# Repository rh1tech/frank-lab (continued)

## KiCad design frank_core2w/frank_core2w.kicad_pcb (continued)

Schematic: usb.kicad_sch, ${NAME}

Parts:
C71: 100nF; C_0603_1608Metric
C72, C73: 100uF; CP_Elec_6.3x6.0
C74, C75, C79, C81, C83: 100nF; C_0603_1608Metric; LCSC C14663
C76, C77, C78, C80, C82, C84, C86, C87, C88: 10uF; C_0603_1608Metric; LCSC C96446
C85: 1uF; C_0603_1608Metric; LCSC C29936
C89, C90: 12pF; C_0603_1608Metric; LCSC C38523
C91: 22pF; C_0603_1608Metric; LCSC C1653
J10, J11: USB4215-03-A; USB_C_Receptacle; LCSC C37616412
JP4: USB Debug; SolderJumper-2_P1.3mm_Open_RoundedPad1.0x1.5mm
JP5: PWR Debug; SolderJumper-2_P1.3mm_Open_RoundedPad1.0x1.5mm
L5: 330R 2A; L_0805_2012Metric; LCSC C76819
L6: 2.2uH; L_Cenker_CKCS3015; LCSC C167747
LD3: Green; LED_0603_1608Metric; LCSC C965804
R49: 10K; R_0603_1608Metric
R50, R51, R52, R53: 5.1K; R_0603_1608Metric; LCSC C23186
R54: 300K; R_0603_1608Metric; LCSC C23024
R55, R58, R62: 100K; R_0603_1608Metric; LCSC C25803
R56: 1M; R_0603_1608Metric; LCSC C22935; not fitted
R57, R60: 1K; R_0603_1608Metric; LCSC C21190
R59: 10K; R_0603_1608Metric; LCSC C2906982
R61: 4.7K; R_0603_1608Metric; LCSC C23162; not fitted
R63: 22K; R_0603_1608Metric; LCSC C31850
S7: SS12D00; Switch_Slide_SS12D00; Mouser Part Number 611-SK12D07VG3NS
S8: SK12D07VG3NS; Switch_Slide_SK12D07VG3NS_PWR; Mouser Part Number 611-SK12D07VG3NS; LCSC C431547
U12: TS3USB221RSER; UQFN-10
U13, U14: TPD4S012DRYR; Mouser Part Number 595-TPD4S012DRYR; LCSC C96506
U15: TPS2116DRL; SOT-583-8; LCSC C3235557
U16: AO3401A; SOT-23-3L_AOS; LCSC C15127
U17: TS3USB221RSER; UQFN-10; LCSC C130085
U18: SY8089AAAC; SOT-23-5; LCSC C78988
U19: CH334F; QFN-24-1EP_4x4mm_P0.5mm_EP2.7x2.7mm; LCSC C5187527
Y4: 12 MHz; Crystal_SMD_3225-4Pin_3.2x2.5mm; LCSC C9002

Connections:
+3V3: C71.1, C81.2, C86.1, C87.1, C91.1, JP4.1 (A), L6.1, R49.1, R57.2, R62.1, S7.2, U12.10 (VCC), U17.10 (VCC); also elsewhere on the board
/CH343P/UD+: U12.1 (1D+); also elsewhere on the board
/CH343P/UD-: U12.2 (1D-); also elsewhere on the board
/RP2350A/D+: U12.3 (2D+); also elsewhere on the board
/RP2350A/D-: U12.4 (2D-); also elsewhere on the board
/RP2350B/D+: U17.8 (D+); also elsewhere on the board
/RP2350B/D-: U17.7 (D-); also elsewhere on the board
/USB/+5V_BUCK: C80.1, C82.1, C83.1, L5.2, U18.1 (EN), U18.4 (IN)
/USB/D2+: J10.6 (DP1), J10.8 (DP2), U13.1 (D+), U17.1 (1D+)
/USB/D2-: J10.5 (DN2), J10.7 (DN1), U13.2 (D-_), U17.2 (1D-)
/USB/DH+: U17.3 (2D+), U19.15 (DPU+)
/USB/DH-: U17.4 (2D-), U19.14 (DMU-)
/USB/DS1+: U19.12 (DP1+); also elsewhere on the board
/USB/DS1-: U19.11 (DM1-); also elsewhere on the board
/USB/DS2+: U19.10 (DP2+); also elsewhere on the board
/USB/DS2-: U19.9 (DM2-); also elsewhere on the board
/USB/DS3+: U19.8 (DP3+); also elsewhere on the board
/USB/DS3-: U19.7 (DM3-); also elsewhere on the board
/USB/OVCUR: U19.1 (~OVCUR); also elsewhere on the board
/USB/PWREN: U19.24 (~PWREN); also elsewhere on the board
/USB/S: JP4.2 (B), R59.2, S7.3, U17.9 (S)
/USB/ST: R56.2, U15.8 (ST)
/USB/USBC_D+: J11.6 (DP1), J11.8 (DP2), U12.8 (D+), U14.1 (D+)
/USB/USBC_D-: J11.5 (DN2), J11.7 (DN1), U12.7 (D-), U14.2 (D-_)
/USB/VBUS_IN: C78.1, C79.2, R58.2, U15.2 (VOUT), U15.7 (VOUT), U16.2 (S)
/USB/VBUS_IN1: C74.2, C76.2, J11.2 (VBUS), J11.11 (VBUS), R54.2, U14.6 (VBUS), U15.3 (VIN1), U15.5 (MODE)
/USB/VBUS_IN2: C75.2, C77.2, J10.2 (VBUS), J10.11 (VBUS), U13.6 (VBUS), U15.6 (VIN2)
/USB/VDD33: C84.2, C85.2, U19.20 (VDD33_{LDO})
/USB/XTAL_N: C89.1, U19.3 (XO), Y4.3
/USB/XTAL_P: C90.1, U19.4 (XI), Y4.1
/USB_SEL: R49.2, U12.9 (S); also elsewhere on the board
GND: C71.2, C72.2, C73.2, C74.1, C75.1, C76.1, C77.1, C78.2, C80.2, C81.1, C82.2, C83.2, C84.1, C85.1, C86.2, C87.2, C88.1, C89.2, C90.2, J10.1 (GND), J10.12 (GND), J10.13 (SHIELD), J11.1 (GND), J11.12 (GND), J11.13 (SHIELD), JP5.1 (A), LD3.1 (K), R50.1, R51.1, R52.1, R53.1, R55.1, R59.1, R61.2, R63.2, S8.2, U12.5 (GND), U12.6 (~OE), U13.4 (GND), U14.4 (GND), U15.1 (GND), U17.5 (GND), U17.6 (~OE), U18.2 (GND), U19.25 (GND), Y4.2, Y4.4; also elsewhere on the board
unnamed: J10.4 (CC1), R50.2
unnamed: J10.10 (CC2), R51.2
unnamed: J11.4 (CC1), R52.2
unnamed: J11.10 (CC2), R53.2
unnamed: JP5.2 (B), R60.2, S8.3
unnamed: LD3.2 (A), R57.1
unnamed: R54.1, R55.2, R56.1, U15.4 (PR1)
unnamed: C79.1, R58.1, R60.1, U16.1 (G)
unnamed: C91.2, R62.2, R63.1, U18.5 (FB)
unnamed: L6.2, U18.3 (LX)
unnamed: R61.1, U19.18 (PSELF)
VBUS: C72.1, C73.1, C88.2, L5.1, U16.3 (D), U19.19 (V5); also elsewhere on the board

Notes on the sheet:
USB-A shared VBUS bulk: C102 + C103 = 200 uF USB 2.0 7.2.4.1: >= 120 uF per hub, may be shared Kyocera AVX APZ0606101M016R 100 uF 16 V aluminium polymer, ESR 30 mOhm

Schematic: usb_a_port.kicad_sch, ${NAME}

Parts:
C95: 100nF; C_0603_1608Metric; LCSC C14663
C96: 10uF; C_0603_1608Metric; LCSC C96446
J12: 676430910; USB_A_Short; LCSC C2798029
R65: 100K; R_0603_1608Metric; LCSC C25803
U21: TPD4S012DRYR; Mouser Part Number 595-TPD4S012DRYR; LCSC C96506
U22: CH217K; SOT-23-6; LCSC C7462749

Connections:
/USB/DS1+: J12.3 (D+), U21.1 (D+); also elsewhere on the board
/USB/DS1-: J12.2 (D-), U21.2 (D-_); also elsewhere on the board
/USB/OVCUR: U22.3 (FLAG#); also elsewhere on the board
/USB/PWREN: U22.4 (EN#); also elsewhere on the board
/USB/USB A Port 1/VBUS_P: C95.1, J12.1 (VBUS), U21.6 (VBUS), U22.1 (VOUT)
GND: C95.2, C96.1, J12.4 (GND), J12.5 (Shield), R65.1, U21.4 (GND), U22.2 (GND); also elsewhere on the board
unnamed: R65.2, U22.5 (ISET)
VBUS: C96.2, U22.6 (VIN); also elsewhere on the board

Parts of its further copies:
C97, C99: 100nF; C_0603_1608Metric; LCSC C14663
C98, C101: 10uF; C_0603_1608Metric; LCSC C96446
J13, J14: 676430910; USB_A_Short; LCSC C2798029
R66, R70: 100K; R_0603_1608Metric; LCSC C25803
U23, U25: TPD4S012DRYR; Mouser Part Number 595-TPD4S012DRYR; LCSC C96506
U24, U27: CH217K; SOT-23-6; LCSC C7462749

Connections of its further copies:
/USB/DS2+: J13.3 (D+), U23.1 (D+); also elsewhere on the board
/USB/DS2-: J13.2 (D-), U23.2 (D-_); also elsewhere on the board
/USB/DS3+: J14.3 (D+), U25.1 (D+); also elsewhere on the board
/USB/DS3-: J14.2 (D-), U25.2 (D-_); also elsewhere on the board
/USB/OVCUR: U24.3 (FLAG#), U27.3 (FLAG#); also elsewhere on the board
/USB/PWREN: U24.4 (EN#), U27.4 (EN#); also elsewhere on the board
/USB/USB A Port 2/VBUS_P: C97.1, J13.1 (VBUS), U23.6 (VBUS), U24.1 (VOUT)
/USB/USB A Port 3/VBUS_P: C99.1, J14.1 (VBUS), U25.6 (VBUS), U27.1 (VOUT)
GND: C97.2, C98.1, C99.2, C101.1, J13.4 (GND), J13.5 (Shield), J14.4 (GND), J14.5 (Shield), R66.1, R70.1, U23.4 (GND), U24.2 (GND), U25.4 (GND), U27.2 (GND); also elsewhere on the board
unnamed: R66.2, U24.5 (ISET)
unnamed: R70.2, U27.5 (ISET)
VBUS: C98.2, C101.2, U24.6 (VIN), U27.6 (VIN); also elsewhere on the board

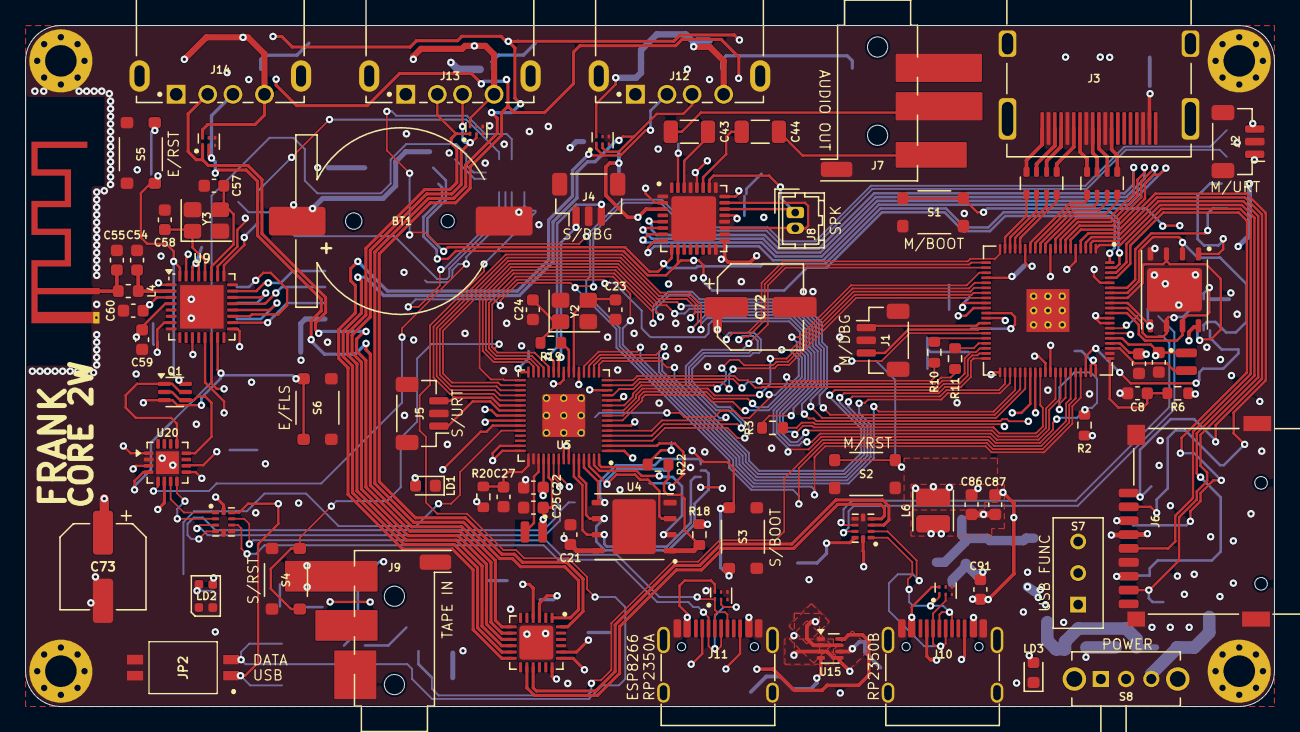
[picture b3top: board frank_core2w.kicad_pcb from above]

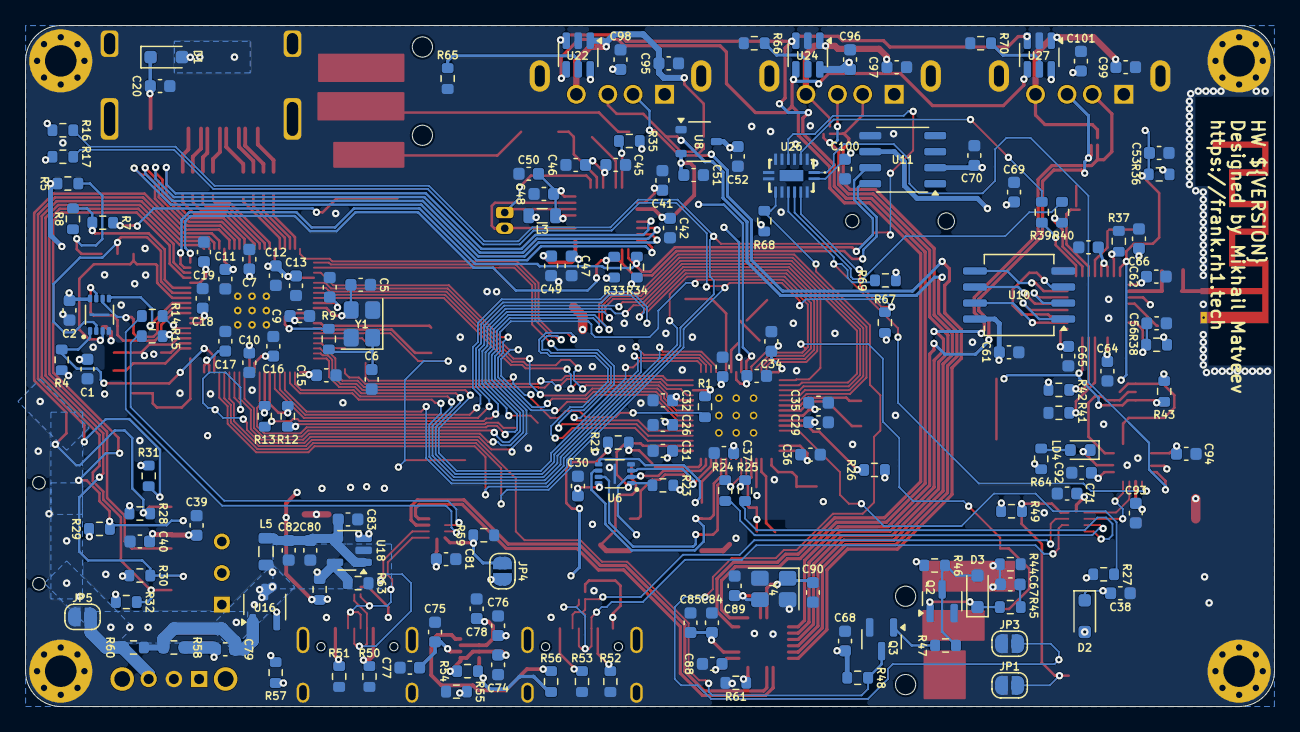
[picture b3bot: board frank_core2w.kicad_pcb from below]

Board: 4 copper layers, 99.0 x 54.0 mm, 253 parts (165 on the bottom side), 203 nets.

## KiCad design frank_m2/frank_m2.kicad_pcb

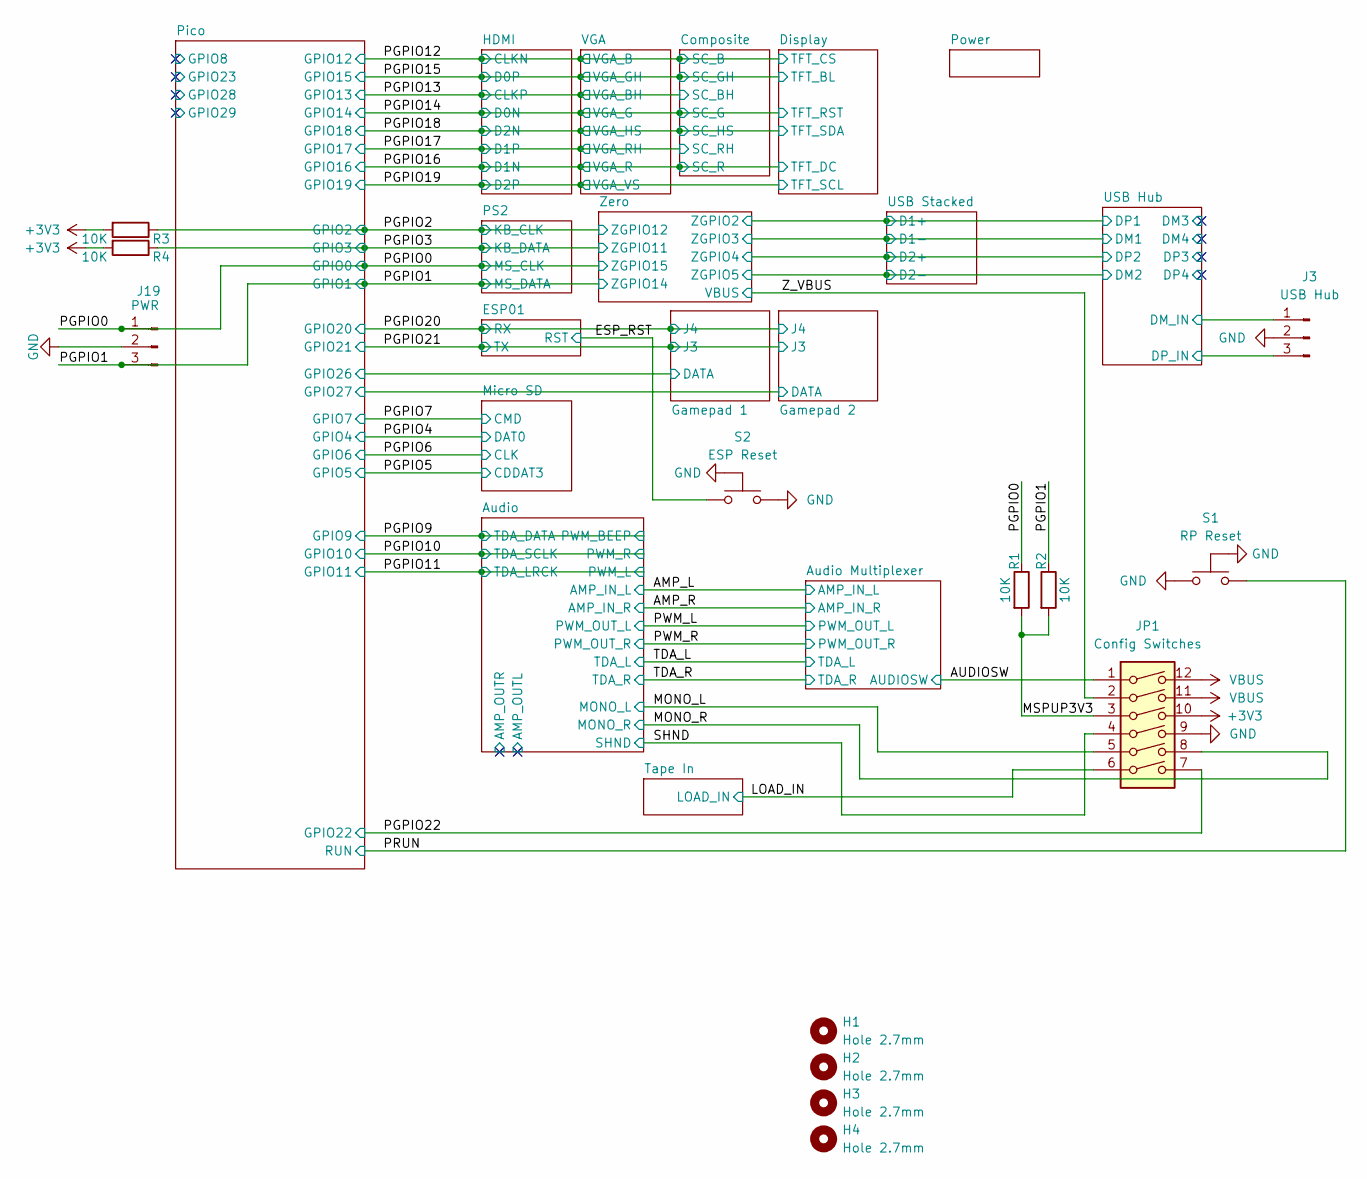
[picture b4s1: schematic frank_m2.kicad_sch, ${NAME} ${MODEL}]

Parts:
H1, H2, H3, H4: Hole 2.7mm; MountingHole_2.7mm
J3: USB Hub; JST_SH_1x03_P1.00mm_Vertical
J19: PWR; JST_SH_1x03_P1.00mm_Vertical_UART
JP1: Config Switches; SOIC-12_P1.27mm
R1, R2, R3, R4: 10K; R_0805_2012Metric
S1: RP Reset; Button_SMD_TS1234VW
S2: ESP Reset; Button_SMD_TS1234VW

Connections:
+3V3: JP1.10, R3.2, R4.2; also elsewhere on the board
/AUDIOSW: JP1.1; also elsewhere on the board
/ESP_RST: S2.1; also elsewhere on the board
/LOAD_IN: JP1.6; also elsewhere on the board
/MONO_L: JP1.5; also elsewhere on the board
/MONO_R: JP1.8; also elsewhere on the board
/MSPUP3V3: JP1.3, R1.2, R2.2
/PGPIO0: J19.1, R1.1; also elsewhere on the board
/PGPIO1: J19.3, R2.1; also elsewhere on the board
/PGPIO2: R3.1; also elsewhere on the board
/PGPIO3: R4.1; also elsewhere on the board
/PGPIO22: JP1.7; also elsewhere on the board
/PRUN: S1.1; also elsewhere on the board
/SHND: JP1.4; also elsewhere on the board
/USB Hub/DM_IN: J3.1; also elsewhere on the board
/USB Hub/DP_IN: J3.3; also elsewhere on the board
/Z_VBUS: JP1.2; also elsewhere on the board
GND: J3.2, J19.2, JP1.9, S1.2, S1.3 (GND), S2.2, S2.3 (GND); also elsewhere on the board
VBUS: JP1.11, JP1.12; also elsewhere on the board

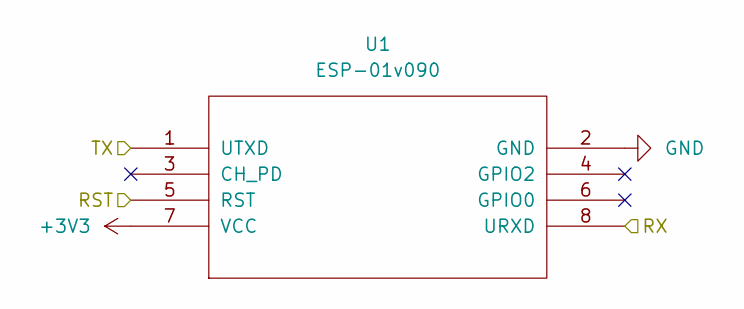
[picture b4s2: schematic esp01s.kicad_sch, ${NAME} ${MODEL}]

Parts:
U1: ESP-01v090; ESP-01

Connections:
+3V3: U1.7 (VCC); also elsewhere on the board
/ESP_RST: U1.5 (RST); also elsewhere on the board
/PGPIO20: U1.8 (URXD); also elsewhere on the board
/PGPIO21: U1.1 (UTXD); also elsewhere on the board
GND: U1.2 (GND); also elsewhere on the board

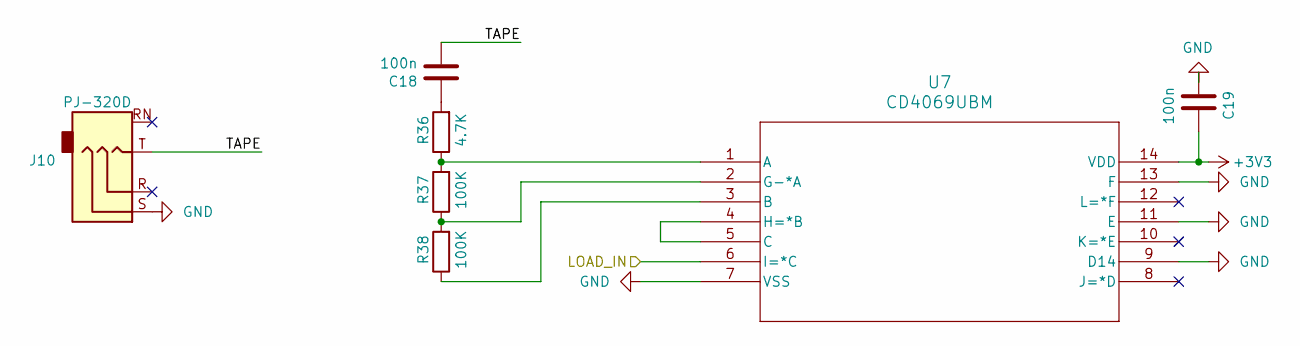
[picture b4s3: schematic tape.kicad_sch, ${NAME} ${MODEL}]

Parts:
C18, C19: 100n; C_0805_2012Metric
J10: PJ-320D; AudioJack_3.5mm_PJ320D
R36: 4.7K; R_0805_2012Metric
R37, R38: 100K; R_0805_2012Metric
U7: CD4069UBM; SOIC-14_P1.27mm

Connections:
+3V3: C19.1, U7.14 (VDD); also elsewhere on the board
/LOAD_IN: U7.6 (I=*C); also elsewhere on the board
/Tape In/TAPE: C18.2, J10.T
GND: C19.2, J10.S, U7.7 (VSS), U7.9 (D14), U7.11 (E), U7.13 (F); also elsewhere on the board
unnamed: C18.1, R36.2
unnamed: R36.1, R37.2, U7.1 (A)
unnamed: R38.1, U7.3 (B)
unnamed: U7.4 (H=*B), U7.5 (C)
unnamed: R37.1, R38.2, U7.2 (G-*A)

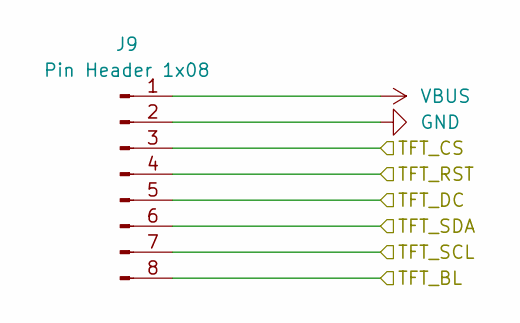
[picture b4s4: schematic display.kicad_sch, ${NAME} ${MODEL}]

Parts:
J9: Pin Header 1x08; JST_GH_1x08_P1.25mm

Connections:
/PGPIO12: J9.3; also elsewhere on the board
/PGPIO14: J9.4; also elsewhere on the board
/PGPIO15: J9.8; also elsewhere on the board
/PGPIO16: J9.5; also elsewhere on the board
/PGPIO18: J9.6; also elsewhere on the board
/PGPIO19: J9.7; also elsewhere on the board
GND: J9.2; also elsewhere on the board
VBUS: J9.1; also elsewhere on the board

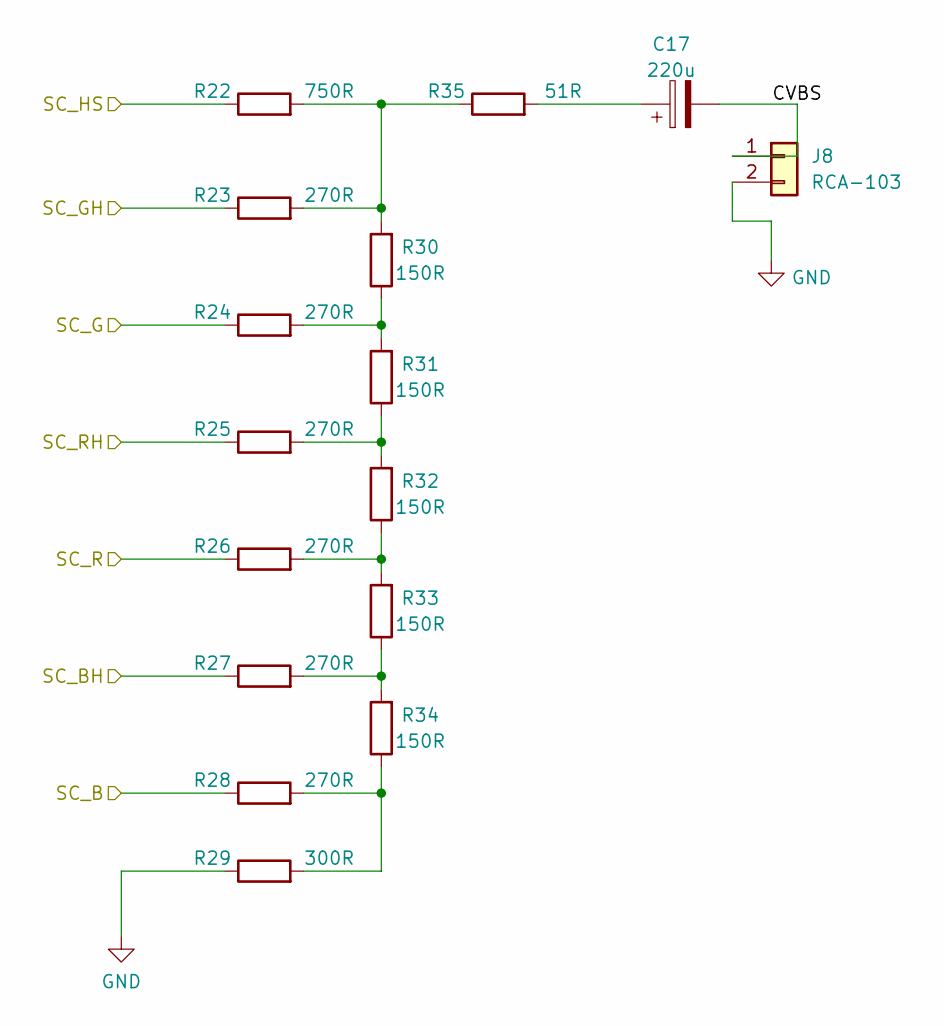
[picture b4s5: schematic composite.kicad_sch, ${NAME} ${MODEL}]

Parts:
C17: 220u; C_Radial_D6.3mm_P2.50mm
J8: RCA-103; BarrelJack_RCJ-012
R22: 750R; R_0805_2012Metric
R23, R24, R25, R26, R27, R28: 270R; R_0805_2012Metric
R29: 300R; R_0805_2012Metric
R30, R31, R32, R33, R34: 150R; R_0805_2012Metric
R35: 51R; R_0805_2012Metric

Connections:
/Composite/CVBS: C17.2, J8.1
/PGPIO12: R28.1; also elsewhere on the board
/PGPIO13: R27.1; also elsewhere on the board
/PGPIO14: R24.1; also elsewhere on the board
/PGPIO15: R23.1; also elsewhere on the board
/PGPIO16: R26.1; also elsewhere on the board
/PGPIO17: R25.1; also elsewhere on the board
/PGPIO18: R22.1; also elsewhere on the board
GND: J8.2, R29.1; also elsewhere on the board
unnamed: C17.1, R35.2
unnamed: R22.2, R23.2, R30.2, R35.1
unnamed: R24.2, R30.1, R31.2
unnamed: R25.2, R31.1, R32.2
unnamed: R26.2, R32.1, R33.2
unnamed: R27.2, R33.1, R34.2
unnamed: R28.2, R29.2, R34.1

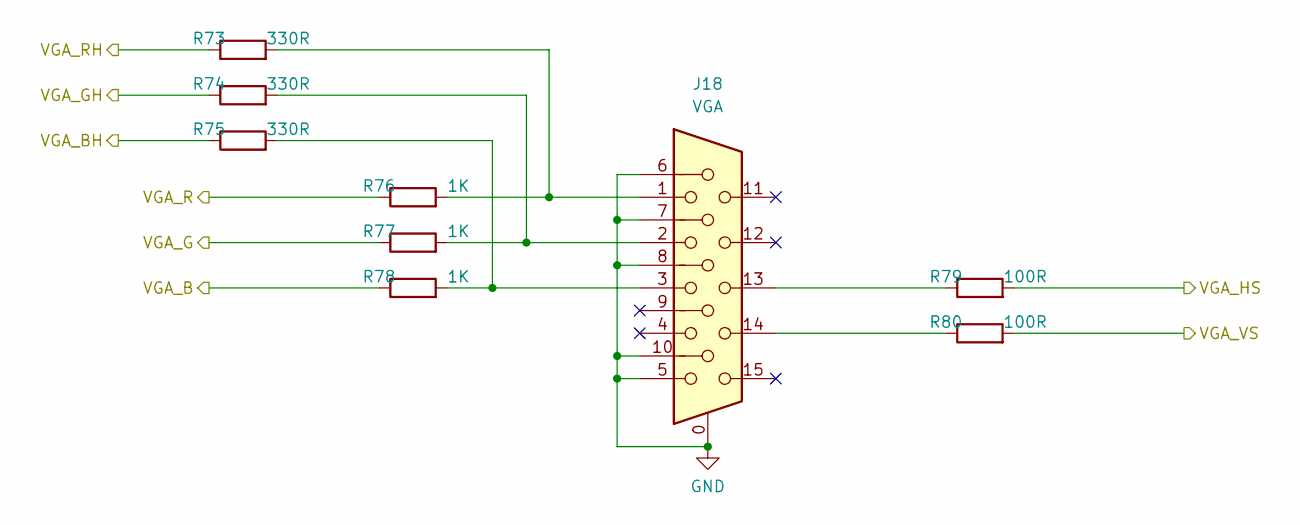
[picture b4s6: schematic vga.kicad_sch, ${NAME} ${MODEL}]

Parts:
J18: VGA; DSUB-15_Female
R73, R74, R75: 330R; R_0805_2012Metric
R76, R77, R78: 1K; R_0805_2012Metric
R79, R80: 100R; R_0805_2012Metric

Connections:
/PGPIO12: R78.1; also elsewhere on the board
/PGPIO13: R75.1; also elsewhere on the board
/PGPIO14: R77.1; also elsewhere on the board
/PGPIO15: R74.1; also elsewhere on the board
/PGPIO16: R76.1; also elsewhere on the board
/PGPIO17: R73.1; also elsewhere on the board
/PGPIO18: R79.2; also elsewhere on the board
/PGPIO19: R80.2; also elsewhere on the board
GND: J18.0, J18.5, J18.6, J18.7, J18.8, J18.10; also elsewhere on the board
unnamed: J18.1, R73.2, R76.2
unnamed: J18.2, R74.2, R77.2
unnamed: J18.3, R75.2, R78.2
unnamed: J18.13, R79.1
unnamed: J18.14, R80.1

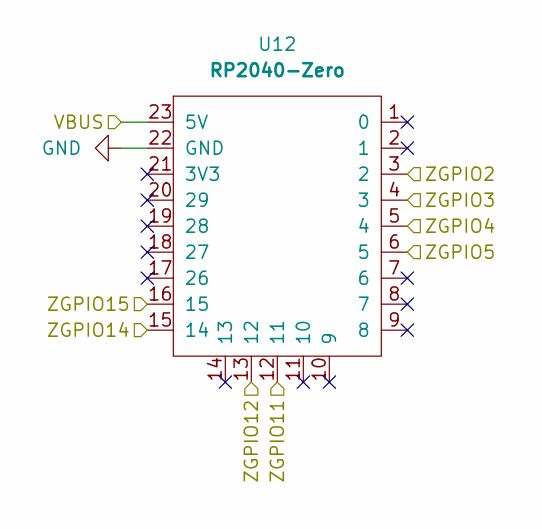
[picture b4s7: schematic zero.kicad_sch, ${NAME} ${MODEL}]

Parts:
U12: RP2040-Zero; RaspberryPi_Zero

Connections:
/PGPIO0: U12.16 (15); also elsewhere on the board
/PGPIO1: U12.15 (14); also elsewhere on the board
/PGPIO2: U12.13 (12); also elsewhere on the board
/PGPIO3: U12.12 (11); also elsewhere on the board
/USB Hub/DM1: U12.4 (3); also elsewhere on the board
/USB Hub/DM2: U12.6 (5); also elsewhere on the board
/USB Hub/DP1: U12.3 (2); also elsewhere on the board
/USB Hub/DP2: U12.5 (4); also elsewhere on the board
/Z_VBUS: U12.23 (5V); also elsewhere on the board
GND: U12.22 (GND); also elsewhere on the board

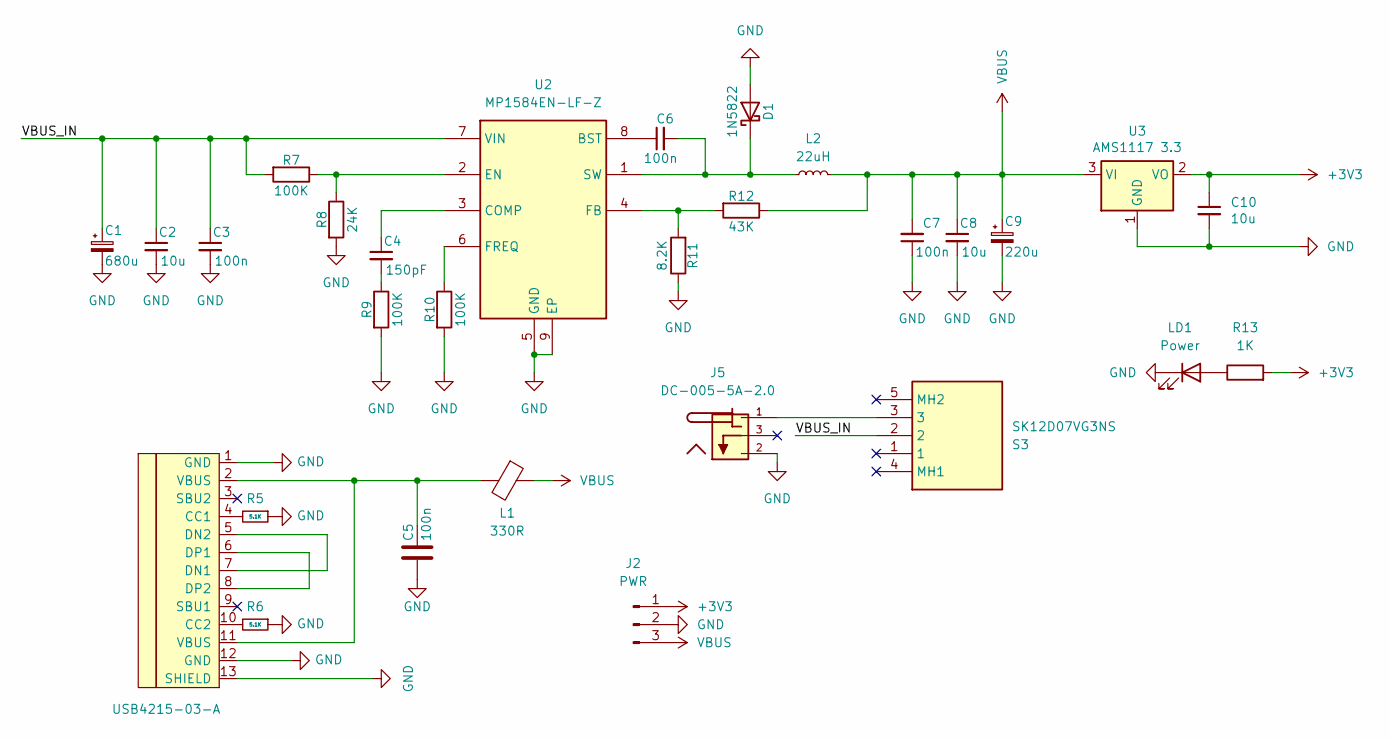
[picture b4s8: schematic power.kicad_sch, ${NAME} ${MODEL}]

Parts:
C1: 680u; C_Radial_D8.0mm_P3.50mm
C2, C8, C10: 10u; C_0805_2012Metric
C3, C5, C6, C7: 100n; C_0805_2012Metric
C4: 150pF; R_0805_2012Metric
C9: 220u; C_Radial_D6.3mm_P2.50mm
D1: 1N5822; D_SMA
J2: PWR; PinHeader_1x03_P2.54mm
J4: USB4215-03-A; USB_C_Receptacle; LCSC C165948
J5: DC-005-5A-2.0; BarrelJack_DC-005; PARTREV A0
L1: 330R; R_0805_2012Metric
L2: 22uH; Inductor_CDRH104RNP
LD1: Power; LED_0805
R5, R6: 5.1K; R_0805_2012Metric
R7, R9, R10: 100K; R_0805_2012Metric
R8: 24K; R_0805_2012Metric
R11: 8.2K; R_0805_2012Metric
R12: 43K; R_0805_2012Metric
R13: 1K; R_0805_2012Metric
S3: SK12D07VG3NS; Switch_Slide_SK12D07VG3NS; Mouser Part Number 611-SK12D07VG3NS
U2: MP1584EN-LF-Z; SOIC-9_P1.27mm; Mouser Part Number 946-MP1584ENLFZ
U3: AMS1117 3.3; SOT-223

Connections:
+3V3: C10.1, J2.1, R13.2, U3.2 (VO); also elsewhere on the board
/Power/VBUS_IN: C1.1, C2.1, C3.1, R7.2, S3.2, U2.7 (VIN)
GND: C1.2, C2.2, C3.2, C5.2, C7.1, C8.2, C9.2, C10.2, D1.2 (A), J2.2, J4.1 (GND), J4.12 (GND), J4.13 (SHIELD), J5.2, LD1.1 (K), R5.1, R6.1, R8.2, R9.2, R10.2, R11.1, U2.5 (GND), U2.9 (EP), U3.1 (GND); also elsewhere on the board
unnamed: C4.2, R9.1
unnamed: C5.1, J4.2 (VBUS), J4.11 (VBUS), L1.2
unnamed: C6.2, D1.1 (K), L2.1, U2.1 (SW)
unnamed: J4.4 (CC1), R5.2
unnamed: J4.10 (CC2), R6.2
unnamed: J4.5 (DN2), J4.7 (DN1)
unnamed: J4.6 (DP1), J4.8 (DP2)
unnamed: J5.1, S3.3
unnamed: LD1.2 (A), R13.1
unnamed: C6.1, U2.8 (BST)
unnamed: C4.1, U2.3 (COMP)
unnamed: R7.1, R8.1, U2.2 (EN)
unnamed: R11.2, R12.2, U2.4 (FB)
unnamed: R10.1, U2.6 (FREQ)
VBUS: C7.2, C8.1, C9.1, J2.3, L1.1, L2.2, R12.1, U3.3 (VI); also elsewhere on the board

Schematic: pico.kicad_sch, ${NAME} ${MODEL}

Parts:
JP2: 3V3 Jumper; Jumper_Solder
U6: Rasberry Pi Pico 1/2; RaspberryPi_Pico

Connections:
+3V3: JP2.2 (B); also elsewhere on the board
/Gamepad 1/DATA: U6.31 (GPIO26_ADC0); also elsewhere on the board
/Gamepad 2/DATA: U6.32 (GPIO27_ADC1); also elsewhere on the board
/PGPIO0: U6.1 (GPIO0); also elsewhere on the board
/PGPIO1: U6.2 (GPIO1); also elsewhere on the board
/PGPIO2: U6.4 (GPIO2); also elsewhere on the board
/PGPIO3: U6.5 (GPIO3); also elsewhere on the board
/PGPIO4: U6.6 (GPIO4); also elsewhere on the board
/PGPIO5: U6.7 (GPIO5); also elsewhere on the board
/PGPIO6: U6.9 (GPIO6); also elsewhere on the board
/PGPIO7: U6.10 (GPIO7); also elsewhere on the board
/PGPIO9: U6.12 (GPIO9); also elsewhere on the board
/PGPIO10: U6.14 (GPIO10); also elsewhere on the board
/PGPIO11: U6.15 (GPIO11); also elsewhere on the board
/PGPIO12: U6.16 (GPIO12); also elsewhere on the board
/PGPIO13: U6.17 (GPIO13); also elsewhere on the board
/PGPIO14: U6.19 (GPIO14); also elsewhere on the board
/PGPIO15: U6.20 (GPIO15); also elsewhere on the board
/PGPIO16: U6.21 (GPIO16); also elsewhere on the board
/PGPIO17: U6.22 (GPIO17); also elsewhere on the board
/PGPIO18: U6.24 (GPIO18); also elsewhere on the board
/PGPIO19: U6.25 (GPIO19); also elsewhere on the board
/PGPIO20: U6.26 (GPIO20); also elsewhere on the board
/PGPIO21: U6.27 (GPIO21); also elsewhere on the board
/PGPIO22: U6.29 (GPIO22); also elsewhere on the board
/PRUN: U6.30 (RUN); also elsewhere on the board
/Pico/GPIO8: U6.11 (GPIO8)
/Pico/GPIO8_1: U6.11 (GPIO8)
/Pico/GPIO23: U6.37 (3V3_EN)
/Pico/GPIO23_1: U6.37 (3V3_EN)
/Pico/GPIO28: U6.34 (GPIO28_ADC2)
/Pico/GPIO28_1: U6.34 (GPIO28_ADC2)
/Pico/GPIO29: U6.35 (ADC_VREF)
/Pico/GPIO29_1: U6.35 (ADC_VREF)
GND: U6.3 (GND), U6.8 (GND), U6.13 (GND), U6.18 (GND), U6.23 (GND), U6.28 (GND), U6.33 (AGND), U6.38 (GND); also elsewhere on the board
unnamed: JP2.1 (A), U6.36 (3V3)
VBUS: U6.40 (VBUS); also elsewhere on the board

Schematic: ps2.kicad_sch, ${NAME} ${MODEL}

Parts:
C11, C12, C13, C14: 100n; C_0805_2012Metric
J6: MDC-036; MiniDIN_6pin_Female
U4: TXS0104EDR; SOIC-14_P1.27mm; Mouser Part Number 595-TXS0104EDR

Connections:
+3V3: C12.1, C13.1, U4.1 (VCCA), U4.8 (OE); also elsewhere on the board
/PGPIO0: U4.4 (A3); also elsewhere on the board
/PGPIO1: U4.5 (A4); also elsewhere on the board
/PGPIO2: U4.2 (A1); also elsewhere on the board
/PGPIO3: U4.3 (A2); also elsewhere on the board
/PS2/KB_CLK_5V: J6.5, U4.13 (B1)
/PS2/KB_DATA_5V: J6.1, U4.12 (B2)
/PS2/MS_CLK_5V: J6.6, U4.11 (B3)
/PS2/MS_DATA_5V: J6.2, U4.10 (B4)
GND: C11.2, C12.2, C13.2, C14.2, J6.3, U4.7 (GND); also elsewhere on the board
VBUS: C11.1, C14.1, J6.4, U4.14 (VCCB); also elsewhere on the board

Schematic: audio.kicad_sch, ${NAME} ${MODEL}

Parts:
J11: PAM L; JST_GH_1x02_P1.25mm
J12: PAM R; JST_GH_1x02_P1.25mm
J13: PJ-320D; AudioJack_3.5mm_PJ320D

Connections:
/Audio/AMP_OUTL: J13.T; also elsewhere on the board
/Audio/AMP_OUTR: J13.R; also elsewhere on the board
/Audio/AMP_PAM_OUTL_M: J11.2; also elsewhere on the board
/Audio/AMP_PAM_OUTL_P: J11.1; also elsewhere on the board
/Audio/AMP_PAM_OUTR_M: J12.2; also elsewhere on the board
/Audio/AMP_PAM_OUTR_P: J12.1; also elsewhere on the board
GND: J13.S; also elsewhere on the board

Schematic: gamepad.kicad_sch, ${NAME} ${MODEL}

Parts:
D3: 3V3; D_miniMELF
J14: GP2; DSUB-9_Male_TopMount
R67: 1K; R_0805_2012Metric

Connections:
/Gamepad 1/DATA: D3.1 (K), R67.1; also elsewhere on the board
/PGPIO20: J14.4; also elsewhere on the board
/PGPIO21: J14.3; also elsewhere on the board
GND: D3.2 (A), J14.8; also elsewhere on the board
unnamed: J14.2, R67.2
VBUS: J14.6; also elsewhere on the board

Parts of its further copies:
D4: 3V3; D_miniMELF
J15: GP2; DSUB-9_Male_TopMount
R68: 1K; R_0805_2012Metric

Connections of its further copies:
/Gamepad 2/DATA: D4.1 (K), R68.1; also elsewhere on the board
/PGPIO20: J15.4; also elsewhere on the board
/PGPIO21: J15.3; also elsewhere on the board
GND: D4.2 (A), J15.8; also elsewhere on the board
unnamed: J15.2, R68.2
VBUS: J15.6; also elsewhere on the board

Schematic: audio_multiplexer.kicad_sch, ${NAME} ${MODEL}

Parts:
C37: 100n; C_0805_2012Metric
R66: 10K; R_0805_2012Metric
U11: 74HC4052D; SOP-16_P1.27mm; Mouser Part Number 771-74HC4052D-T

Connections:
/AMP_L: U11.13 (1Z); also elsewhere on the board
/AMP_R: U11.3 (2Z); also elsewhere on the board
/AUDIOSW: R66.2, U11.10 (S0); also elsewhere on the board
/PWM_L: U11.12 (1Y0); also elsewhere on the board
/PWM_R: U11.1 (2Y0); also elsewhere on the board
/TDA_L: U11.14 (1Y1); also elsewhere on the board
/TDA_R: U11.5 (2Y1); also elsewhere on the board
GND: C37.1, R66.1, U11.2 (2Y2), U11.4 (2Y3), U11.6 (~E), U11.7 (VEE), U11.8 (GND), U11.9 (S1), U11.11 (1Y3), U11.15 (1Y2); also elsewhere on the board
VBUS: C37.2, U11.16 (VCC); also elsewhere on the board

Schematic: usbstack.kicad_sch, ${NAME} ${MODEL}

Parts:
C39, C40: 10u; C_0805_2012Metric
J17: SS-52100-004; USB_A_Stacked
R69, R70, R71, R72: 22R; R_0805_2012Metric

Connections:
/USB Hub/DM1: R70.1; also elsewhere on the board
/USB Hub/DM2: R72.1; also elsewhere on the board
/USB Hub/DP1: R69.1; also elsewhere on the board
/USB Hub/DP2: R71.1; also elsewhere on the board
GND: C39.2, C40.2, J17.4 (GND1), J17.8 (GND2), J17.SH (Shield); also elsewhere on the board
unnamed: J17.3 (D1+), R69.2
unnamed: J17.2 (D1-), R70.2
unnamed: J17.7 (D2+), R71.2
unnamed: J17.6 (D2-), R72.2
VBUS: C39.1, C40.1, J17.1 (VBUS1), J17.5 (VBUS2); also elsewhere on the board

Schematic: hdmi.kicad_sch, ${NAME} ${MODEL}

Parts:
C16: 100n; C_0805_2012Metric
D2: 1N5819WS; D_SOD-323
J7: DC3RX19JA2; HDMI_Female
R14, R15, R16, R17, R18, R19, R20, R21: 270R; R_0805_2012Metric

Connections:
/PGPIO12: R16.2; also elsewhere on the board
/PGPIO13: R20.2; also elsewhere on the board
/PGPIO14: R14.2; also elsewhere on the board
/PGPIO15: R17.2; also elsewhere on the board
/PGPIO16: R18.2; also elsewhere on the board
/PGPIO17: R21.2; also elsewhere on the board
/PGPIO18: R15.2; also elsewhere on the board
/PGPIO19: R19.2; also elsewhere on the board
GND: C16.2, J7.2 (G_D2), J7.5 (G_D1), J7.8 (G_D0), J7.11 (G_CLK), J7.17 (G_DDC/CEC), J7.20 (SHIELD1), J7.21 (SHIELD2), J7.22 (SHIELD3), J7.23 (SHIELD4); also elsewhere on the board
unnamed: C16.1, D2.1 (K), J7.18 (+5V)
unnamed: J7.12 (CLKN), R16.1
unnamed: J7.10 (CLKP), R20.1
unnamed: J7.9 (D0N), R14.1
unnamed: J7.7 (D0P), R17.1
unnamed: J7.6 (D1N), R18.1
unnamed: J7.4 (D1P), R21.1
unnamed: J7.3 (D2N), R15.1
unnamed: J7.1 (D2P), R19.1
VBUS: D2.2 (A); also elsewhere on the board

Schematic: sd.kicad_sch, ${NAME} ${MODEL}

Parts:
C38: 100n; C_0805_2012Metric
J16: 104031-0811; MicroSD_SMD_Long

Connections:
+3V3: C38.2, J16.4 (VDD); also elsewhere on the board
/PGPIO4: J16.7 (DAT0); also elsewhere on the board
/PGPIO5: J16.2 (DAT3/CD); also elsewhere on the board
/PGPIO6: J16.5 (CLK); also elsewhere on the board
/PGPIO7: J16.3 (CMD); also elsewhere on the board
GND: C38.1, J16.6 (VSS), J16.SH (SHIELD); also elsewhere on the board

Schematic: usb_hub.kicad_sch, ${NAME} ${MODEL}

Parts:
C15: 4.7u; C_0805_2012Metric; LCSC C1746
U5: MW7211A; SOP-16_P1.27mm

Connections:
/USB Hub/DM1: U5.7 (DM3); also elsewhere on the board
/USB Hub/DM2: U5.5 (DM2); also elsewhere on the board
/USB Hub/DM3: U5.3 (DM1)
/USB Hub/DM4: U5.1 (DM0)
/USB Hub/DM_IN: U5.10 (DMU); also elsewhere on the board
/USB Hub/DP1: U5.8 (DP3); also elsewhere on the board
/USB Hub/DP2: U5.6 (DP2); also elsewhere on the board
/USB Hub/DP3: U5.4 (DP1)
/USB Hub/DP4: U5.2 (DP0)
/USB Hub/DP_IN: U5.11 (DPU); also elsewhere on the board
GND: C15.2, U5.15 (GND), U5.16 (GND); also elsewhere on the board
unnamed: U5.12 (VD33), U5.14 (VD3)
VBUS: C15.1, U5.13 (VDD5); also elsewhere on the board

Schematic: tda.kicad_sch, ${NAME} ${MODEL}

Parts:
C22, C24: 10u; C_0805_2012Metric
C23: 100n; C_0805_2012Metric
R47: 100R; R_0805_2012Metric
R48, R49: 470R; R_0805_2012Metric
U8: TDA1387T; SO-8

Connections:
/PGPIO9: U8.3 (DATA); also elsewhere on the board
/PGPIO10: U8.1 (SCLK); also elsewhere on the board
/PGPIO11: U8.2 (LRCK); also elsewhere on the board
/TDA_L: R49.2, U8.6 (A_LEFT); also elsewhere on the board
/TDA_R: R48.1, U8.8 (A_RIGHT); also elsewhere on the board
GND: C22.2, C23.2, C24.2, R48.2, R49.1, U8.4 (AGND); also elsewhere on the board
unnamed: C24.1, U8.7 (FLT)
unnamed: C22.1, C23.1, R47.1, U8.5 (VA)
VBUS: R47.2; also elsewhere on the board

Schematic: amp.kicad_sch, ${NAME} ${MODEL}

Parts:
C25, C30, C35: 1u; C_0805_2012Metric
C26, C27, C28, C32, C33: 10u; C_0805_2012Metric
C29, C34: 100n; C_0805_2012Metric
C31: 10u; C_Radial_D6.3mm_P2.50mm
C36: 100u; C_Radial_D6.3mm_P2.50mm
R50, R52: 2K; R_0805_2012Metric
R51, R53, R54, R55, R56, R57, R58, R61, R65: 10K; R_0805_2012Metric
R59, R60: 47K; R_0805_2012Metric
R62: 100R; R_0805_2012Metric
R63, R64: 20K; R_0805_2012Metric
U9: PAM8403D; SOP-16_P1.27mm; Mouser Part Number 700-MAX232CSE
U10: LM358; SO-8

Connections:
/AMP_L: C26.1, R51.1; also elsewhere on the board
/AMP_R: C27.1, R53.1; also elsewhere on the board
/Audio/AMP_OUTL: C32.2, R63.2; also elsewhere on the board
/Audio/AMP_OUTR: C33.2, R64.2; also elsewhere on the board
/Audio/AMP_PAM_OUTL_M: U9.3 (-OUTL); also elsewhere on the board
/Audio/AMP_PAM_OUTL_P: U9.1 (+OUT_L); also elsewhere on the board
/Audio/AMP_PAM_OUTR_M: U9.14 (-OUT_R); also elsewhere on the board
/Audio/AMP_PAM_OUTR_P: U9.16 (+OUT_R); also elsewhere on the board
/MONO_L: C25.1, R50.1, R51.2; also elsewhere on the board
/MONO_R: C30.1, R52.1, R53.2; also elsewhere on the board
/SHND: R65.2, U9.12 (SHND); also elsewhere on the board
GND: C28.1, C29.2, C31.2, C34.1, C35.2, C36.2, R50.2, R52.2, R55.1, R63.1, R64.1, U9.2 (PGND), U9.11 (GND), U9.15 (PGND), U10.4 (V-); also elsewhere on the board
unnamed: C25.2, R56.2
unnamed: C26.2, R57.2
unnamed: C27.2, R58.2
unnamed: C30.2, R61.2
unnamed: C32.1, R59.1, U10.7
unnamed: C33.1, R60.1, U10.1
unnamed: R56.1, U9.7 (INL)
unnamed: R61.1, U9.10 (INR)
unnamed: C29.1, U9.8 (VREF)
unnamed: C28.2, R54.1, R55.2, U10.3 (+), U10.5 (+)
unnamed: R58.1, R60.2, U10.2 (-)
unnamed: R57.1, R59.2, U10.6 (-)
unnamed: C31.1, C34.2, R54.2, R62.2, U10.8 (V+)
VBUS: C35.1, C36.1, R62.1, R65.1, U9.4 (PVDD), U9.5 (MUTE), U9.6 (VDD), U9.13 (PVDD); also elsewhere on the board

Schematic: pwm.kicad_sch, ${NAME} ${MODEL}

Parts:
C20, C21: 47n; C_0805_2012Metric
R39, R41: 10K; R_0805_2012Metric
R40, R42, R43, R44: 2K; R_0805_2012Metric
R45, R46: 1K; R_0805_2012Metric

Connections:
/PGPIO9: R43.1, R44.1; also elsewhere on the board
/PGPIO10: R46.2; also elsewhere on the board
/PGPIO11: R45.2; also elsewhere on the board
/PWM_L: R41.2, R42.1; also elsewhere on the board
/PWM_R: R39.2, R40.1; also elsewhere on the board
GND: C20.2, C21.2, R40.2, R42.2; also elsewhere on the board
unnamed: C20.1, R39.1, R43.2, R46.1
unnamed: C21.1, R41.1, R44.2, R45.1
